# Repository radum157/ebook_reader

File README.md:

###### Copyright Radu Marin 2025
## README
# OpenBook

# Table of content

1. [Hardware details](#hardware-details)
2. [Design](#design)
3. [Diagram](#diagram)
4. [Bill of Materials](#bill-of-materials)

# Hardware details

OpenBook is an e-reader platform based on ESP32-C6 with E-Paper display technology. This document outlines the hardware architecture, component selection, and design considerations.

### Primary components:

**ESP32-C6 Microcontroller**
- ESP32-C6-WROOM-1-N8 module

**E-Paper Display**
- Waveshare 7.5” e-Paper V2
- Connected via 24-pin FPC header
- MBR0530 diodes in drive circuit for voltage management
- Dedicated power regulation

### Power Management

**Battery System**
- CELLEVIA BATTERIES LP584174 3.7V / 1800mAh LiPo battery
- MCP73831 LiPo charging controller
- MAX17048G+T10 fuel gauge
- JST connector

**Voltage Regulation**
- XC6220A331MR-G LDO for stable 3.3V
- DMG2305UX-7 MOSFETs for reverse polarity protection
- BD5229G-TR supervisor for clean resets

### Storage & Memory

**SD Card**
- Full-size SD slot with presence detection
- SPI mode communication

**External Flash**
- W25Q512JVEIQ NOR Flash
- SPI interface with ESD protection

**RTC**
- DS3231SN precision timekeeper
- Super-cap backup power
- I2C interface shared with sensors

### Sensors & IO

**Environmental Sensing**
- BME688 for temperature, humidity, pressure, air quality
- I2C bus connection

**UI**
- Boot, Change and Reset buttons
- Test pads integrated as exposed copper

### Communication interfaces:

 * I2C:
    - Used for communication with the BME688 sensor and DS3231SN RTC.
    - Send/Receive data to/from the sensor and RTC.
    - Also used for MAX17048G+T10 fuel gauge monitoring
    - QWIIC connector for expansion

 * SPI:
    - Used for communication with the E-Paper display and SD Card.
    - The ESP32-C6 uses SPI to send data to the display and read/write to the SD card.
    - Also used for the external W25Q512JVEIQ flash memory

 * GPIO:
    - Used for the reset/boot button and other custom functionalities.

**USB-C**
- USB4110-GF-A connector
- USBLC6-2SC6Y for ESD protection on data lines
- Charging and data transfer

**SPI Configuration**
- 10MHz clock rate
- Individual chip selects
- Shared data and clock lines

**I2C Setup**
- 400kHz standard mode
- 4.7kΩ pull-ups
- Shared among BME688, MAX17048G+T10, DS3231SN, and QWIIC port

**USB Interface**
- 5V, 500mA input

### Pins used:

| Pin | Function | Connected To | Why |
|-----|----------|--------------|-----------|
| GPIO0 | BOOT | Boot/Reset Button | Flash mode access |
| GPIO1/2 | UART | USB-Serial | Debugging |
| GPIO3-4, 6-7 | SD Card | SD interface | Dedicated SD pins for reliability |
| GPIO5 | EPD_CS | E-Paper CS line | Display control |
| GPIO8 | FLASH_CS | External Flash | Flash memory selection |
| GPIO9-11 | SPI Bus | Shared SPI | Central bus for all SPI devices |
| GPIO12-13 | I2C Bus | Sensors & expansion | Shared I2C for all sensors |
| GPIO14-16 | EPD Control | E-Paper control signals | Timing control |
| GPIO17 | ADC | Battery voltage | Power monitoring |
| GPIO19-23 | EPD Data | E-Paper data lines | Display data transfer |

### Power consumption:
- Display refresh: ~125mA @ 3.3V
- Idle: ~25mA @ 3.3V
- Deep sleep: ~150μA @ 3.3V
- Duty cycle: 1-2 weeks typical use (1800mAh battery)

# Design

The final design of the PCB and 3D model attempt to minimize noise interference and maximize ease-of-use, while maintaining all of the core functionalities of OpenBook.

**Metoda de rezolvare / Probleme intampinate**

Schematic:

- Implemented following the electric design of the e-book reader
- Approved errors in relation to power pins

PCB 2D:

- Measured the dimensions and distances on the board and added the components accordingly (only on top layer)
- Approved errors in relation to board outline clearance (components in question needed to be closer to the enclosure)
- Added net classes to separate power lines from regular ones
- Created the power lines on top, with no vias, then the rest, all while attempting to optimize routing
- Added GND on top and bottom with no holes
- Via stitching close to ESP32

PCB 3D:

- Ensured soldermask layer is visible and at a small distance from the circuitry on the board
- Added accurate models for all components in use

Final 3D design:

- Added the pcb to the enclosure
- Modified the box shape for the SD, buttons etc. to fit
- Created a model for the Li-Po battery and 7.5” display
- Put everything together to ensure it fits

<br>

**The end result**

<br>

# Diagram

# Bill of Materials

| Qty | Value | Device | Parts | CHECK_PRICES | DATASHEET |
|:---:|:------|:-------|:------|:------------|:----------|
| 1 | 0.47 | ESP32_WROVER_EAGLE-LTSPICE_RR0402 | R3 | [YAGEO](https://componentsearchengine.com/part-view/R0402%201%25%20100%20K%20(RC0402FR-07100KL)/YAGEO) | [Datasheet](https://www.yageo.com/upload/media/product/products/datasheet/rchip/PYu-RC_Group_51_RoHS_L_12.pdf) |
| 1 | 100k | ESP32_WROVER_EAGLE-LTSPICE_RR0402 | R1_PWRUSB | [YAGEO](https://componentsearchengine.com/part-view/R0402%201%25%20100%20K%20(RC0402FR-07100KL)/YAGEO) | [Datasheet](https://www.yageo.com/upload/media/product/products/datasheet/rchip/PYu-RC_Group_51_RoHS_L_12.pdf) |
| 8 | 100nF | EAGLE-LTSPICE_CC0402 | C1, C2, C4_USB, C6, C8, C9, C10, C_DELAY | [YAGEO](https://componentsearchengine.com/part-view/CC0402MRX5R5BB106/YAGEO) | [Datasheet](https://ro.mouser.com/datasheet/2/447/upy_gphc_x5r_4v_to_50v-3461255.pdf) |
| 1 | 100uF TANT | RCL_CPOL-EUCT3528 | C3 | [Mouser](https://eu.mouser.com/ProductDetail/KYOCERA-AVX/TPSB106K025T1800?qs=qSfuJ%252Bfl%2Fd753zkuSz4nrg%3D%3D) | [Datasheet](https://eu.mouser.com/datasheet/2/40/TPS_AUTO-3165215.pdf) |
| 16 | 10k | ESP32_WROVER_EAGLE-LTSPICE_RR0402 | R1, R1-PINH, R1-PINH1, R2-PINH, R2-PINH1, R4, R5, R6, R7, R8, R9, R10, R_BOOT, R_CHANGE, R_CL1, R_RESET | [YAGEO](https://componentsearchengine.com/part-view/R0402%201%25%20100%20K%20(RC0402FR-07100KL)/YAGEO) | [Datasheet](https://www.yageo.com/upload/media/product/products/datasheet/rchip/PYu-RC_Group_51_RoHS_L_12.pdf) |
| 1 | 10uF | EAGLE-LTSPICE_CC0402 | C7 | [YAGEO](https://componentsearchengine.com/part-view/CC0402MRX5R5BB106/YAGEO) | [Datasheet](https://ro.mouser.com/datasheet/2/447/upy_gphc_x5r_4v_to_50v-3461255.pdf) |
| 1 | 112A-TAAR-R03_ATTEND | 112A-TAAR-R03_ATTEND | J10 | [Comet](https://store.comet.srl.ro/Catalogue/Product/43497/) | [Datasheet](https://www.attend.com.tw/en/product.php?act=view&id=253) |
| 1 | 15 | ESP32_WROVER_EAGLE-LTSPICE_RR0402 | R_CAPACITOR | [YAGEO](https://componentsearchengine.com/part-view/R0402%201%25%20100%20K%20(RC0402FR-07100KL)/YAGEO) | [Datasheet](https://www.yageo.com/upload/media/product/products/datasheet/rchip/PYu-RC_Group_51_RoHS_L_12.pdf) |
| 1 | 1m | SJ | SJ1 | - | - |
| 1 | 1uF | EAGLE-LTSPICE_CC0402 | C5 | [YAGEO](https://componentsearchengine.com/part-view/CC0402MRX5R5BB106/YAGEO) | [Datasheet](https://ro.mouser.com/datasheet/2/447/upy_gphc_x5r_4v_to_50v-3461255.pdf) |
| 10 | 1uF/50V | EAGLE-LTSPICE_CC0402 | EPD_C1, EPD_C2, EPD_C5, EPD_C6, EPD_C7, EPD_C8, EPD_C9, EPD_C10, EPD_C11, EPD_C12 | [YAGEO](https://componentsearchengine.com/part-view/CC0402MRX5R5BB106/YAGEO) | [Datasheet](https://ro.mouser.com/datasheet/2/447/upy_gphc_x5r_4v_to_50v-3461255.pdf) |
| 1 | 2.2 | ESP32_WROVER_EAGLE-LTSPICE_RR0402 | R2 | [YAGEO](https://componentsearchengine.com/part-view/R0402%201%25%20100%20K%20(RC0402FR-07100KL)/YAGEO) | [Datasheet](https://www.yageo.com/upload/media/product/products/datasheet/rchip/PYu-RC_Group_51_RoHS_L_12.pdf) |
| 1 | 200 | ESP32_WROVER_EAGLE-LTSPICE_RR0402 | R1_BAT | [YAGEO](https://componentsearchengine.com/part-view/R0402%201%25%20100%20K%20(RC0402FR-07100KL)/YAGEO) | [Datasheet](https://www.yageo.com/upload/media/product/products/datasheet/rchip/PYu-RC_Group_51_RoHS_L_12.pdf) |
| 2 | 20V/4.2A/52mO/1.4W | ESP32_WROVER_SPARKFUN-DISCRETESEMI_MOSFET_PCH-DMG2305UX-7 | Q1, Q2 | [Diodes Inc](https://componentsearchengine.com/part-view/DMG2305UX-7/Diodes%20Incorporated) | [Datasheet](https://www.diodes.com/assets/Datasheets/DMG2305UX.pdf) |
| 1 | 2k | ESP32_WROVER_EAGLE-LTSPICE_RR0402 | R2_BAT | [YAGEO](https://componentsearchengine.com/part-view/R0402%201%25%20100%20K%20(RC0402FR-07100KL)/YAGEO) | [Datasheet](https://www.yageo.com/upload/media/product/products/datasheet/rchip/PYu-RC_Group_51_RoHS_L_12.pdf) |
| 5 | 4.7uF | EAGLE-LTSPICE_CC0402 | C1_BAT, C1_BAT1, C1_BAT2, C2_BAT, C5_USB | [YAGEO](https://componentsearchengine.com/part-view/CC0402MRX5R5BB106/YAGEO) | [Datasheet](https://ro.mouser.com/datasheet/2/447/upy_gphc_x5r_4v_to_50v-3461255.pdf) |
| 1 | 4.7uF/25V | EAGLE-LTSPICE_CC0402 | C4 | [YAGEO](https://componentsearchengine.com/part-view/CC0402MRX5R5BB106/YAGEO) | [Datasheet](https://ro.mouser.com/datasheet/2/447/upy_gphc_x5r_4v_to_50v-3461255.pdf) |
| 2 | 5k1 | ESP32_WROVER_EAGLE-LTSPICE_RR0402 | R2-USB, R2-USB1 | [YAGEO](https://componentsearchengine.com/part-view/R0402%201%25%20100%20K%20(RC0402FR-07100KL)/YAGEO) | [Datasheet](https://www.yageo.com/upload/media/product/products/datasheet/rchip/PYu-RC_Group_51_RoHS_L_12.pdf) |
| 1 | 68uH | 744043680IND_4828-WE-TPC_WRE | L1 | [Mouser](https://eu.mouser.com/ProductDetail/Wurth-Elektronik/744043680?qs=PGXP4M47uW6VkZq%252BkzjrHA%3D%3D) | [Datasheet](https://www.we-online.com/components/products/datasheet/744043680.pdf) |
| 1 | BD5229G-TR | BD5229G-TR | IC1 | [ROHM](https://componentsearchengine.com/part-view/BD5229G-TR/ROHM%20Semiconductor) | [Datasheet](https://fscdn.rohm.com/en/products/databook/datasheet/ic/power/voltage_detector/bd52xxg-e.pdf) |
| 1 | BME688 | ESP32_WROVER_BME680_BME680 | SENSOR2 | [SnapEDA](https://www.snapeda.com/parts/BME680/Bosch/view-part/?welcome=home) | [Datasheet](https://www.snapeda.com/parts/BME680/Bosch%20Sensortec/datasheet/) |
| 3 | BUTTON_CUSYOMV1 | BUTTON_CUSYOMV1 | BOOT_BUTTON, CHANGE_BUTTON, RESET_BUTTON | [Panasonic](https://industry.panasonic.com/global/en/products/control/switch/light-touch/number/evqpuj02k) | [Datasheet](https://www.alldatasheet.com/datasheet-pdf/pdf/537835/PANASONIC/EVQPUJ02K.html) |
| 1 | CPH3225A | CPH3225A | C10_SUPERCAP | [SnapEDA](https://www.snapeda.com/parts/CPH3225A/Seiko+Instruments/view-part/?ref=eda) | [Datasheet](https://www.snapeda.com/parts/CPH3225A/Seiko%20Instruments/datasheet/) |
| 1 | DS3231SN# | DS3231SN# | U3 | [SnapEDA](https://www.snapeda.com/parts/DS3231SN%23/Analog+Devices/view-part/?ref=eda) | [Datasheet](https://www.snapeda.com/parts/DS3231SN%23/Analog%20Devices/datasheet/) |
| 1 | ESP32-C6-WROOM-1-N8 | ESP32-C6-WROOM-1-N8 | U2 | [SnapEDA](https://www.snapeda.com/parts/ESP32-C6-WROOM-1-N8/Espressif+Systems/view-part/?ref=eda) | [Datasheet](https://www.snapeda.com/parts/ESP32-C6-WROOM-1-N8/Espressif%20Systems/datasheet/) |
| 1 | ESP32C6_VARISTORCN1812 | ESP32C6_VARISTORCN1812 | PFMF.050.1 | [Digikey](https://www.digikey.com/en/products/detail/abracon-llc/AMCV-1812H-180-T/4245629) | [Datasheet](https://abracon.com/Magnetics/circuit_protection/AMCV-1812H.pdf) |
| 2 | ESP32_WROVER_AVX-SD0805S020S1R0 | ESP32_WROVER_AVX-SD0805S020S1R0 | D2, D7 | [Mouser](https://eu.mouser.com/ProductDetail/KYOCERA-AVX/SD0805S020S1R0?qs=jCA%252BPfw4LHbpkAoSnwrdjw%3D%3D) | [Datasheet](http://datasheets.avx.com/schottky.pdf) |
| 1 | ESP32_WROVER_SPARKFUN-IC-POWER_MCP73831 | ESP32_WROVER_SPARKFUN-IC-POWER_MCP73831 | MCP73831 | [Mouser](https://www.mouser.co.uk/ProductDetail/Microchip-Technology/MCP73831T-5ACI-OT?qs=hH%252BOa0VZEiAcgAcEkuamXg%3D%3D) | [Datasheet](https://www.mouser.co.uk/datasheet/2/268/MCP73831_Family_Data_Sheet_DS20001984H-3441711.pdf) |
| 1 | FH34SRJ-24S-0.5SH_99_ | FH34SRJ-24S-0.5SH_99_ | J1 | [Hirose](https://componentsearchengine.com/part-view/FH34SRJ-24S-0.5SH(99)/Hirose) | [Datasheet](https://www.hirose.com/en/product/document?clcode=CL0580-1255-6-99&productname=FH34SRJ-24S-0.5SH(99)&series=FH34SRJ&documenttype=SpecSheet&lang=en&documentid=0000414526) |
| 1 | MAX17048G+T10 | MAX17048G+T10 | U4 | [SnapEDA](https://www.snapeda.com/parts/MAX17048G+T10/Analog+Devices/view-part/?ref=eda) | [Datasheet](https://www.snapeda.com/parts/MAX17048G+T10/Analog%20Devices/datasheet/) |
| 3 | MBR0530 | MBR0530 | D3, D4, D5 | [SnapEDA](https://www.snapeda.com/parts/MBR0530/Onsemi/view-part/?ref=eda) | [Datasheet](https://www.snapeda.com/parts/MBR0530/ON%20Semiconductor/datasheet/) |
| 6 | PGB1010603MR | PGB1010603MR | D6, D8, D9, D10, D11, D12 | [SnapEDA](https://www.snapeda.com/parts/PGB1010603MR/Littelfuse/view-part/?ref=eda) | [Datasheet](https://www.snapeda.com/parts/PGB1010603MR/Littelfuse%20Inc./datasheet/) |
| 1 | QWIIC_RIGHT_ANGLE | QWIIC_CONNECTORJS-1MM | J3 | [SnapEDA](https://www.snapeda.com/parts/PRT-14417/SparkFun%20Electronics/view-part/?ref=search&t=qwiic) | [Datasheet](https://www.snapeda.com/parts/PRT-14417/SparkFun%20Electronics/datasheet/) |
| 1 | SAMACSYS_PARTS_USB4110-GF-A | SAMACSYS_PARTS_USB4110-GF-A | J2 | [GCT](https://componentsearchengine.com/part-view/USB4110-GF-A/GCT%20(GLOBAL%20CONNECTOR%20TECHNOLOGY)) | [Datasheet](https://ro.mouser.com/datasheet/2/837/GCT_USB4110_Product_Drawing___20k_cycles-3455479.pdf) |
| 1 | SI1308EDL-T1-GE3 | SI1308EDL-T1-GE3 | Q3 | [SnapEDA](https://www.snapeda.com/parts/SI1308EDL-T1-GE3/Vishay+Siliconix/view-part/?ref=eda) | [Datasheet](https://www.snapeda.com/parts/SI1308EDL-T1-GE3/Vishay%20Siliconix/datasheet/) |
| 1 | SMD-LED0603 | ADAFRUIT_LEDCHIP-LED0603 | CHG_LED | [SnapEDA](https://www.snapeda.com/parts/KP-1608SURCK/Kingbright/view-part/?ref=search&t=LED%200603) | [Datasheet](https://www.snapeda.com/parts/KP-1608SURCK/Kingbright/datasheet/) |
| 17 | TPTP20R | TPTP20R | TP1, TP2, TP3, TP4, TP5, TP6, TP7, TP8, TP9, TP10, TP11, TP12, TP13, TP14, TP15, TP16, TP17 | - | - |
| 1 | USBLC6-2SC6Y | USBLC6-2SC6Y | D1 | [SnapEDA](https://www.snapeda.com/parts/USBLC6-2SC6Y/STMicroelectronics/view-part/?ref=eda) | [Datasheet](https://www.snapeda.com/parts/USBLC6-2SC6Y/STMicroelectronics/datasheet/) |
| 1 | W25Q512JVEIQ | W25Q512JVEIQ | U1 | [SnapEDA](https://www.snapeda.com/parts/W25Q512JVEIQ/Winbond+Electronics/view-part/?ref=eda) | [Datasheet](https://www.snapeda.com/parts/W25Q512JVEIQ/Winbond%20Electronics/datasheet/) |
| 1 | XC6220A331MR-G | XC6220A331MR-G | IC4 | [Torex](https://componentsearchengine.com/part-view/XC6220A331MR-G/Torex) | [Datasheet](https://eu.mouser.com/datasheet/2/760/xc6220-3371556.pdf) |

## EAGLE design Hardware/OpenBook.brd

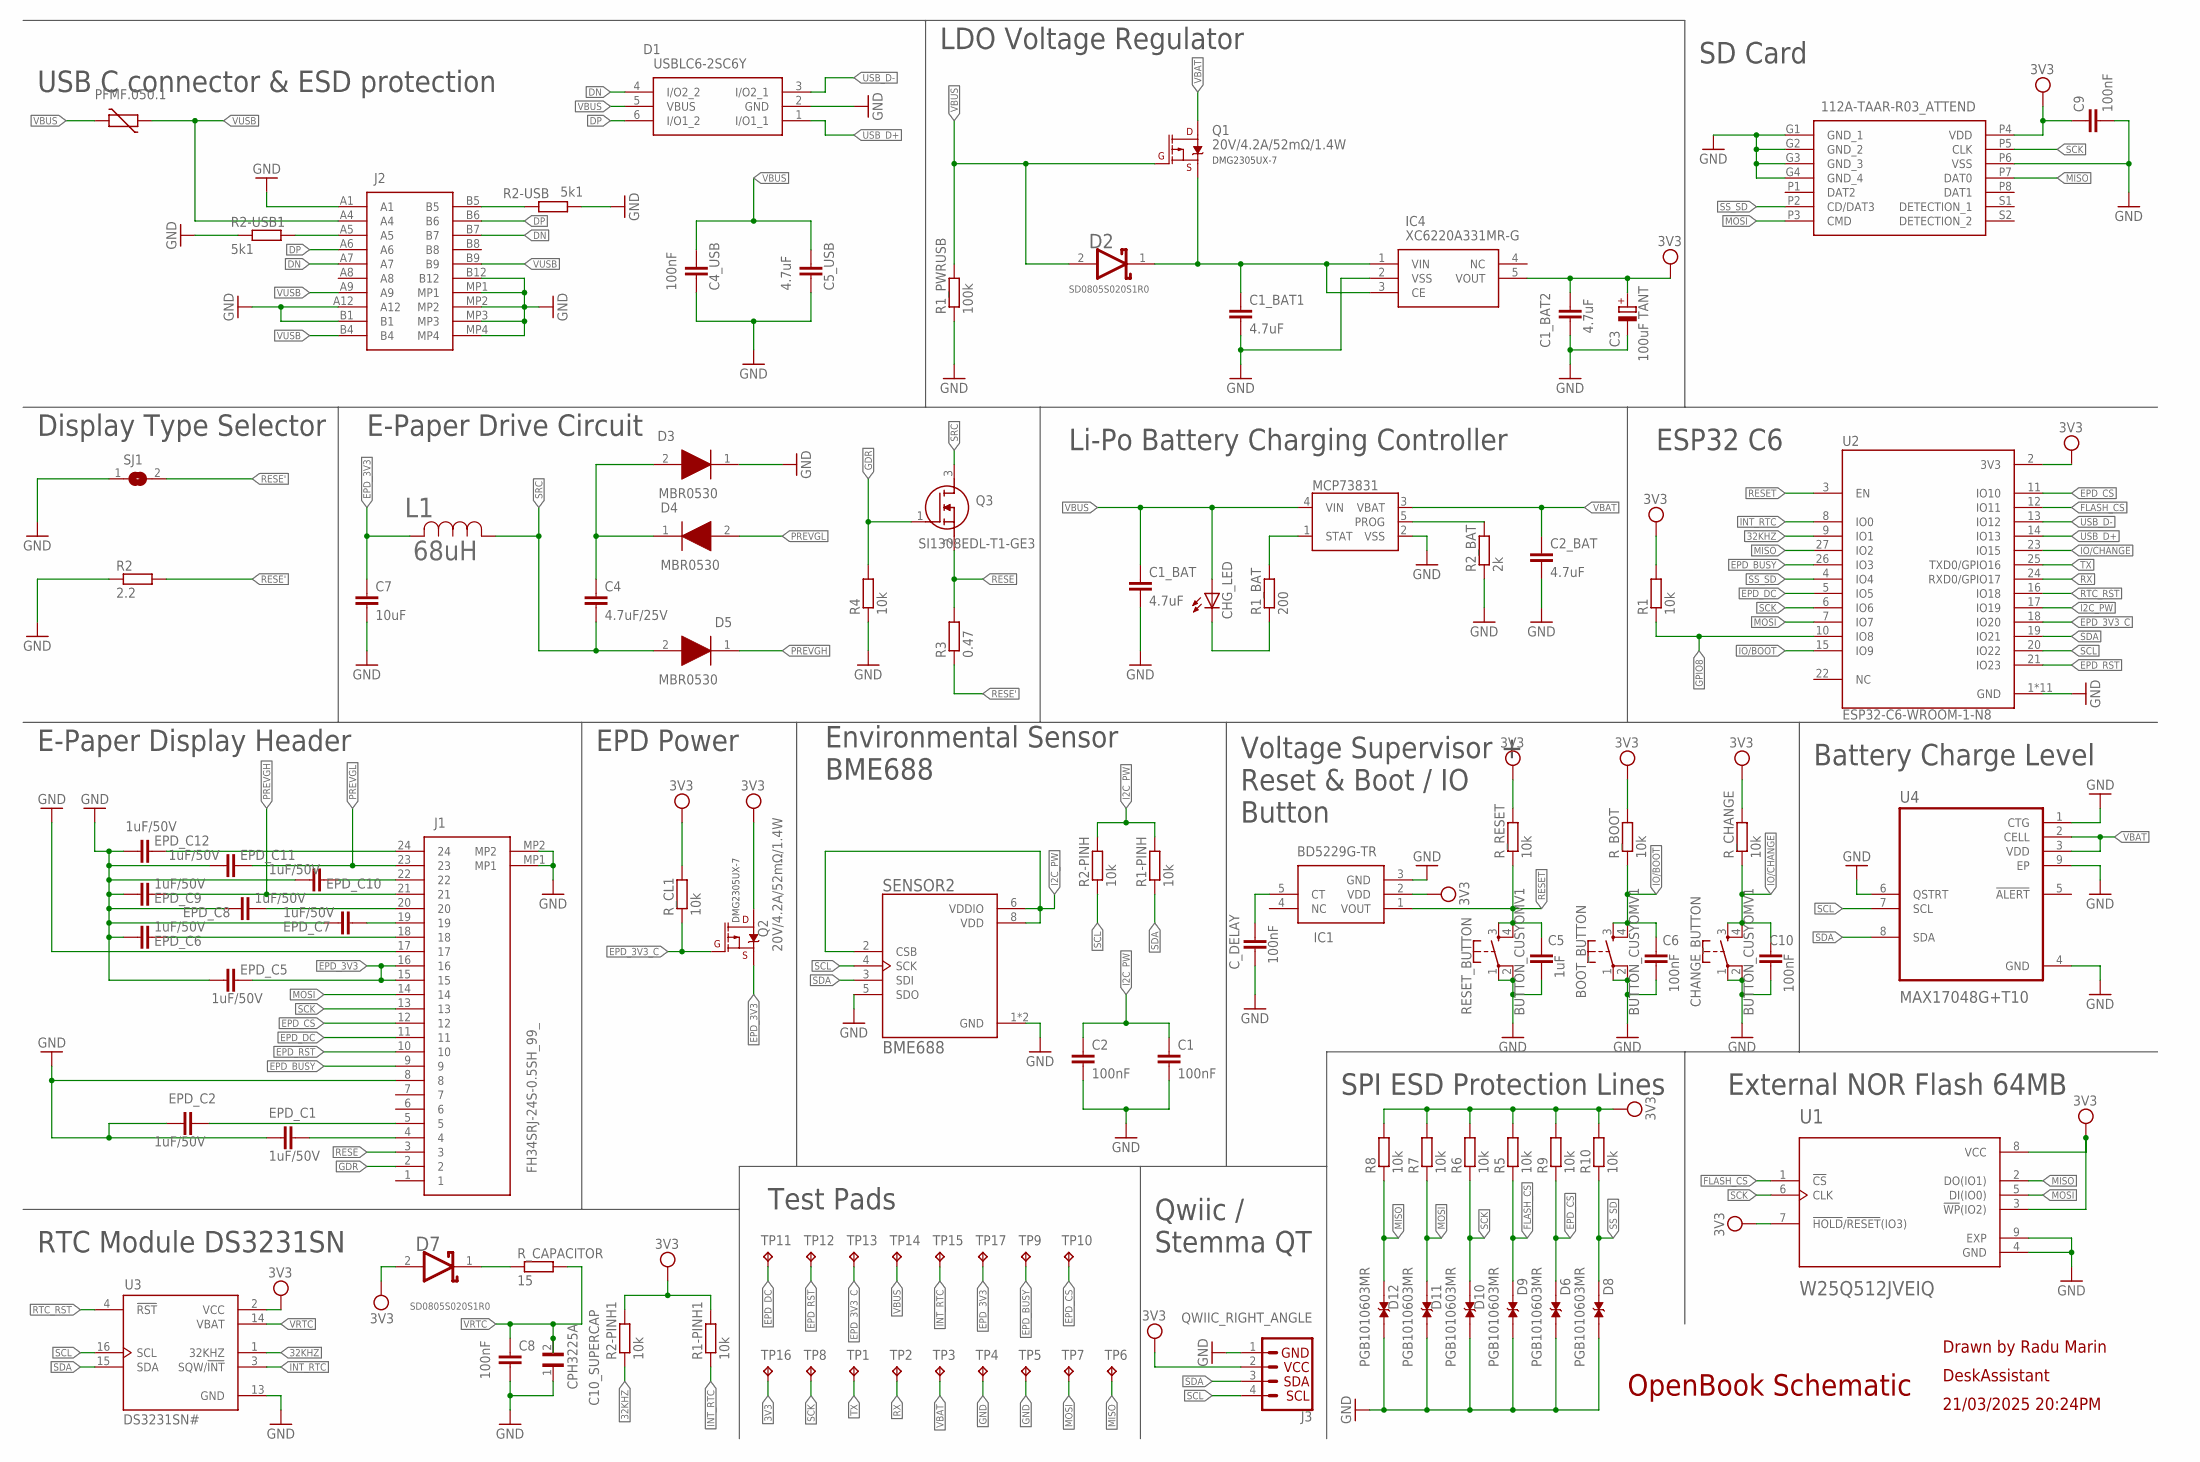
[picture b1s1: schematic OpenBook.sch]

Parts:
BOOT_BUTTON: BUTTON_CUSYOMV1; MYBUTTON
C1, C2, C4_USB, C6, C8, C9, C10: 100nF; EAGLE-LTSPICE_C0402
C1_BAT, C1_BAT1, C1_BAT2, C2_BAT, C5_USB: 4.7uF; EAGLE-LTSPICE_C0402
C3: 100uF TANT; RCL_CT3528
C4: 4.7uF/25V; EAGLE-LTSPICE_C0402
C5: 1uF; EAGLE-LTSPICE_C0402
C7: 10uF; EAGLE-LTSPICE_C0402
C10_SUPERCAP: CPH3225A; CAPCP3225X100N
CHANGE_BUTTON: BUTTON_CUSYOMV1; MYBUTTON
CHG_LED: SMD-LED0603; ADAFRUIT_CHIP-LED0603
C_DELAY: 100nF; EAGLE-LTSPICE_C0402
D1: USBLC6-2SC6Y; SOT95P280X145-6N
D2, D7: ESP32_WROVER_AVX---SD0805S020S1R0_AVX_SD0805S020S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; ESP32_WROVER_AVX---SD0805S020S1R0_AVX_SD0805S020S1R0_0
D3, D4, D5: MBR0530; SOD3716X135N
D6, D8, D9, D10, D11, D12: PGB1010603MR; DIOC1608X36N
EPD_C1, EPD_C2, EPD_C5, EPD_C6, EPD_C7, EPD_C8, EPD_C9, EPD_C10, EPD_C11, EPD_C12: 1uF/50V; EAGLE-LTSPICE_C0402
IC1: BD5229G-TR; SOT95P280X125-5N
IC4: XC6220A331MR-G; SOT95P280X120-5N
J1: FH34SRJ-24S-0.5SH_99_; FH34SRJ24S05SH99
J2: SAMACSYS_PARTS_USB4110-GF-A; SAMACSYS_PARTS_USB4110GFA
J3: QWIIC_RIGHT_ANGLE; JST04_1MM_RA
J10: 112A-TAAR-R03_ATTEND; 112ATAARR03ATTEND
L1: 68uH; IND_4828-WE-TPC_WRE
MCP73831: ESP32_WROVER_SPARKFUN-IC-POWER_MCP73831; ESP32_WROVER_SPARKFUN-IC-POWER_SOT23-5
PFMF.050.1: ESP32C6_VARISTORCN1812; ESP32C6_VARISTOR_CT/CN1812
Q1, Q2: 20V/4.2A/52mΩ/1.4W; ESP32_WROVER_SPARKFUN-DISCRETESEMI_SOT23-3
Q3: SI1308EDL-T1-GE3; SOT65P210X110-3N
R1, R1-PINH, R1-PINH1, R2-PINH, R2-PINH1, R4, R5, R6, R7, R8, R9, R10: 10k; ESP32_WROVER_EAGLE-LTSPICE_R0402
R1_BAT: 200; ESP32_WROVER_EAGLE-LTSPICE_R0402
R1_PWRUSB: 100k; ESP32_WROVER_EAGLE-LTSPICE_R0402
R2: 2.2; ESP32_WROVER_EAGLE-LTSPICE_R0402
R2-USB, R2-USB1: 5k1; ESP32_WROVER_EAGLE-LTSPICE_R0402
R2_BAT: 2k; ESP32_WROVER_EAGLE-LTSPICE_R0402
R3: 0.47; ESP32_WROVER_EAGLE-LTSPICE_R0402
RESET_BUTTON: BUTTON_CUSYOMV1; MYBUTTON
R_BOOT: 10k; ESP32_WROVER_EAGLE-LTSPICE_R0402
R_CAPACITOR: 15; ESP32_WROVER_EAGLE-LTSPICE_R0402
R_CHANGE: 10k; ESP32_WROVER_EAGLE-LTSPICE_R0402
R_CL1: 10k; ESP32_WROVER_EAGLE-LTSPICE_R0402
R_RESET: 10k; ESP32_WROVER_EAGLE-LTSPICE_R0402
SENSOR2: BME688; ESP32_WROVER_BME680_PSON80P300X300X100-8N
SJ1: 1m; SJ
TP1, TP2, TP3, TP4, TP5, TP6, TP7, TP8, TP9, TP10, TP11, TP12, TP13, TP14, TP15, TP16, TP17: TPTP20R; TP20R
U1: W25Q512JVEIQ; SON127P600X800X80-9N
U2: ESP32-C6-WROOM-1-N8; XCVR_ESP32-C6-WROOM-1-N8
U3: DS3231SN#; SOIC127P1032X265-16N
U4: MAX17048G+T10; SON50P200X200X80-9N

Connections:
3V3: C1_BAT2.1, C3.+, C9.1, D7.2 (ANODE), IC1.2 (VDD), IC4.5 (VOUT), J3.2, J10.P4 (VDD), Q2.3 (D), R1.2, R1-PINH1.2, R2-PINH1.2, R5.2, R6.2, R7.2, R8.2, R9.2, R10.2, R_BOOT.2, R_CHANGE.2, R_CL1.2, R_RESET.2, TP16.TP, U1.3 (!WP!(IO2)), U1.7 (!HOLD!/!RESET!(IO3)), U1.8 (VCC), U2.2 (3V3), U3.2 (VCC)
32KHZ: R2-PINH1.1, U2.9 (IO1), U3.1 (32KHZ)
DN: D1.4 (I/O2_2), J2.A7, J2.B7
DP: D1.6 (I/O1_2), J2.A6, J2.B6
EPD_3V3: C7.1, EPD_C5.1, J1.15, J1.16, L1.2, Q2.2 (S), TP17.TP
EPD_3V3_C: Q2.1 (G), R_CL1.1, TP13.TP, U2.18 (IO20)
EPD_BUSY: J1.9, TP9.TP, U2.26 (IO3)
EPD_CS: D6.2, J1.12, R9.1, TP10.TP, U2.11 (IO10)
EPD_DC: J1.11, TP11.TP, U2.5 (IO5)
EPD_RST: J1.10, TP12.TP, U2.21 (IO23)
FLASH_CS: D9.2, R5.1, U1.1 (!CS), U2.12 (IO11)
GDR: J1.2, Q3.1 (G), R4.2
GND: BOOT_BUTTON.1, BOOT_BUTTON.2, C1.2, C1_BAT.2, C1_BAT1.2, C1_BAT2.2, C2.2, C2_BAT.2, C3.-, C4_USB.2, C5.2, C5_USB.2, C6.2, C7.2, C8.2, C9.2, C10.2, C10_SUPERCAP.1, CHANGE_BUTTON.1, CHANGE_BUTTON.2, C_DELAY.2, D1.2 (GND), D3.1 (K), D6.1, D8.1, D9.1, D10.1, D11.1, D12.1, EPD_C1.2, EPD_C2.2, EPD_C5.2, EPD_C6.2, EPD_C7.2, EPD_C8.2, EPD_C9.2, EPD_C10.2, EPD_C11.2, EPD_C12.2, IC1.3 (GND), IC4.2 (VSS), J1.8, J1.17, J1.MP1, J1.MP2, J2.A1, J2.A12, J2.B1, J2.B12, J2.MP1, J2.MP2, J2.MP3, J2.MP4, J3.1, J10.G1 (GND_1), J10.G2 (GND_2), J10.G3 (GND_3), J10.G4 (GND_4), J10.P6 (VSS), MCP73831.2 (VSS), R1_PWRUSB.1, R2.1, R2-USB.2, R2-USB1.1, R2_BAT.1, R4.1, RESET_BUTTON.1, RESET_BUTTON.2, SENSOR2.1 (GND), SENSOR2.5 (SDO), SENSOR2.7 (GND), SJ1.1, TP4.TP, TP5.TP, U1.4 (GND), U1.9 (EXP), U2.1 (GND), U2.28 (GND), U2.29_1 (GND), U2.29_2 (GND), U2.29_3 (GND), U2.29_4 (GND), U2.29_5 (GND), U2.29_6 (GND), U2.29_7 (GND), U2.29_8 (GND), U2.29_9 (GND), U3.13 (GND), U4.1 (CTG), U4.4 (GND), U4.6 (QSTRT), U4.9 (EP)
GPIO8: R1.1, U2.10 (IO8)
I2C_PW: C1.1, C2.1, R1-PINH.2, R2-PINH.2, SENSOR2.2 (CSB), SENSOR2.6 (VDDIO), SENSOR2.8 (VDD), U2.17 (IO19)
INT_RTC: R1-PINH1.1, TP15.TP, U2.8 (IO0), U3.3 (SQW/!INT)
IO/BOOT: BOOT_BUTTON.3, BOOT_BUTTON.4, C6.1, R_BOOT.1, U2.15 (IO9)
IO/CHANGE: C10.1, CHANGE_BUTTON.3, CHANGE_BUTTON.4, R_CHANGE.1, U2.23 (IO15)
MISO: D12.2, J10.P7 (DAT0), R8.1, TP6.TP, U1.2 (DO(IO1)), U2.27 (IO2)
MOSI: D11.2, J1.14, J10.P3 (CMD), R7.1, TP7.TP, U1.5 (DI(IO0)), U2.7 (IO7)
unnamed: J2.B5, R2-USB.1
unnamed: J2.A5, R2-USB1.2
unnamed: CHG_LED.C, R1_BAT.1
unnamed: C1_BAT1.1, D2.1 (CATHODE), IC4.1 (VIN), IC4.3 (CE), Q1.2 (S)
unnamed: C4.1, D3.2 (A), D4.1 (K)
unnamed: MCP73831.1 (STAT), R1_BAT.2
unnamed: MCP73831.5 (PROG), R2_BAT.2
unnamed: EPD_C12.1, J1.24
unnamed: EPD_C10.1, J1.22
unnamed: EPD_C8.1, J1.20
unnamed: EPD_C7.1, J1.19
unnamed: EPD_C6.1, J1.18
unnamed: EPD_C2.1, J1.5
unnamed: EPD_C1.1, J1.4
unnamed: C_DELAY.1, IC1.5 (CT)
unnamed: D7.1 (CATHODE), R_CAPACITOR.1
PREVGH: D5.1 (K), EPD_C9.1, J1.21
PREVGL: D4.2 (A), EPD_C11.1, J1.23
RESE: J1.3, Q3.2 (S), R3.2
RESE': R2.2, R3.1, SJ1.2
RESET: C5.1, IC1.1 (VOUT), RESET_BUTTON.3, RESET_BUTTON.4, R_RESET.1, U2.3 (EN)
RTC_RST: U2.16 (IO18), U3.4 (!RST)
RX: TP2.TP, U2.24 (RXD0/GPIO17)
SCK: D10.2, J1.13, J10.P5 (CLK), R6.1, TP8.TP, U1.6 (CLK), U2.6 (IO6)
SCL: J3.4, R2-PINH.1, SENSOR2.4 (SCK), U2.20 (IO22), U3.16 (SCL), U4.7 (SCL)
SDA: J3.3, R1-PINH.1, SENSOR2.3 (SDI), U2.19 (IO21), U3.15 (SDA), U4.8 (SDA)
SRC: C4.2, D5.2 (A), L1.1, Q3.3 (D)
SS_SD: D8.2, J10.P2 (CD/DAT3), R10.1, U2.4 (IO4)
TX: TP1.TP, U2.25 (TXD0/GPIO16)
USB_D+: D1.1 (I/O1_1), U2.14 (IO13)
USB_D-: D1.3 (I/O2_1), U2.13 (IO12)
VBAT: C2_BAT.1, MCP73831.3 (VBAT), Q1.3 (D), TP3.TP, U4.2 (CELL), U4.3 (VDD)
VBUS: C1_BAT.1, C4_USB.1, C5_USB.1, CHG_LED.A, D1.5 (VBUS), D2.2 (ANODE), MCP73831.4 (VIN), PFMF.050.1.2, Q1.1 (G), R1_PWRUSB.2, TP14.TP
VRTC: C8.1, C10_SUPERCAP.2, R_CAPACITOR.2, U3.14 (VBAT)
VUSB: J2.A4, J2.A9, J2.B4, J2.B9, PFMF.050.1.1

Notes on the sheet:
DMG2305UX-7
SD0805S020S1R0
USB C connector & ESD protection
LDO Voltage Regulator
SD Card
ESP32 C6
Display Type Selector
E-Paper Drive Circuit
Li-Po Battery Charging Controller
E-Paper Display Header
EPD Power
Voltage Supervisor + Reset & Boot / IO Button
Battery Charge Level
RTC Module DS3231SN
Test Pads
Qwiic / Stemma QT
SPI ESD Protection Lines
External NOR Flash 64MB
Environmental Sensor BME688
OpenBook Schematic
Drawn by Radu Marin
DeskAssistant
21/03/2025 20:24PM

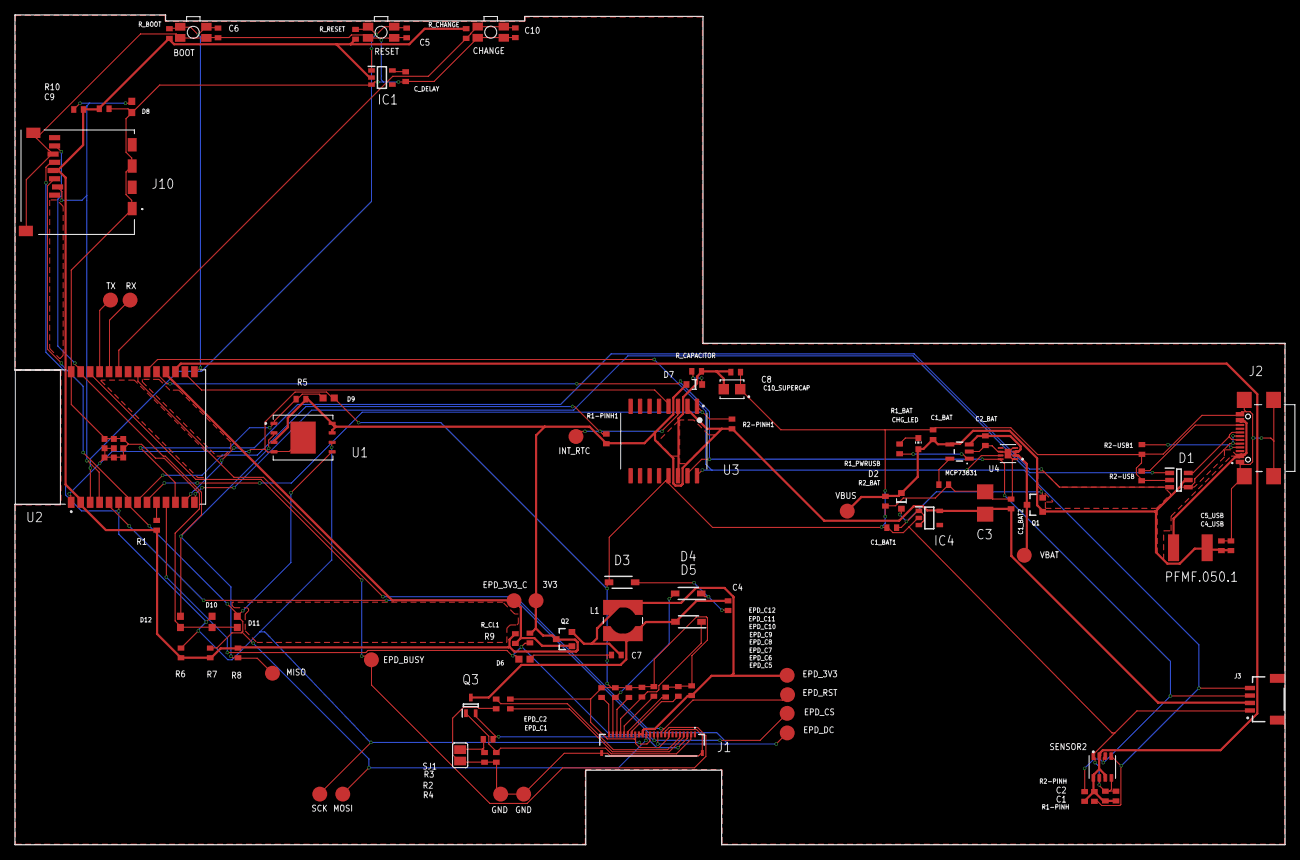
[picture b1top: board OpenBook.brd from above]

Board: 2 copper layers, 170.2 x 111.2 mm, 103 parts (0 on the bottom side), 55 nets.

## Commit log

2025-03-21 Create LICENSE
2025-03-21 Added schematic
2025-03-21 Update sch
2025-03-31 Add PCB
2025-04-03 Add 3D model
2025-04-03 Add manufacturing
2025-04-03 Update files. Add README data.
2025-04-03 v1.0.0
2025-04-03 fix(readme): v1.0.1
2025-04-03 fix(svg): fixed diagram data
2025-04-04 fix(3d): SJ and exploded
2025-04-04 v1.1.0 fix(bom): add datasheets
2025-04-05 fix(exploded)
2025-04-06 fix(readme): png links
2025-04-06 fix(bom): fill in missing data
2025-04-10 fix(issue#3): reduced vias
2025-04-10 fix(issue#2): fix explosion not appearing
2025-04-10 fix(issue#1): verified readme data and added details
2025-04-10 patch: fix errors after fixes
2025-04-11 fix(pcb): board height
2025-04-14 fix(height): adjust for PCB thickness change
2025-04-15 feat(PCB): add dimensions

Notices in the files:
parts and their libraries:
COPYRIGHT: Copyright (C) 2024 Ultra Librarian. All rights reserved.
